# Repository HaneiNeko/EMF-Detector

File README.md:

# EMF Detector

Original project : https://www.instructables.com/Attiny85-EMF-detector/

## What is an EMF detector ?
An EMF detector is a device used to measure the presence and intensity of electromagnetic fields in a particular area.

Using in the ghosts detection 👻, this device is very famous.

## How does it work ?
An antena detect a electromagnetic fields, and depending on the electromagnetic field's force, a led will be turn on, and make a noise.

## This project
This project is an EMF detector using the Arduino framework.

## Schematics

## Usage
1. Use the schematic for create the PCB
2. Push the code into the microcontroller
3. Print the case (optional)
4. Enjoy ! 👻😉

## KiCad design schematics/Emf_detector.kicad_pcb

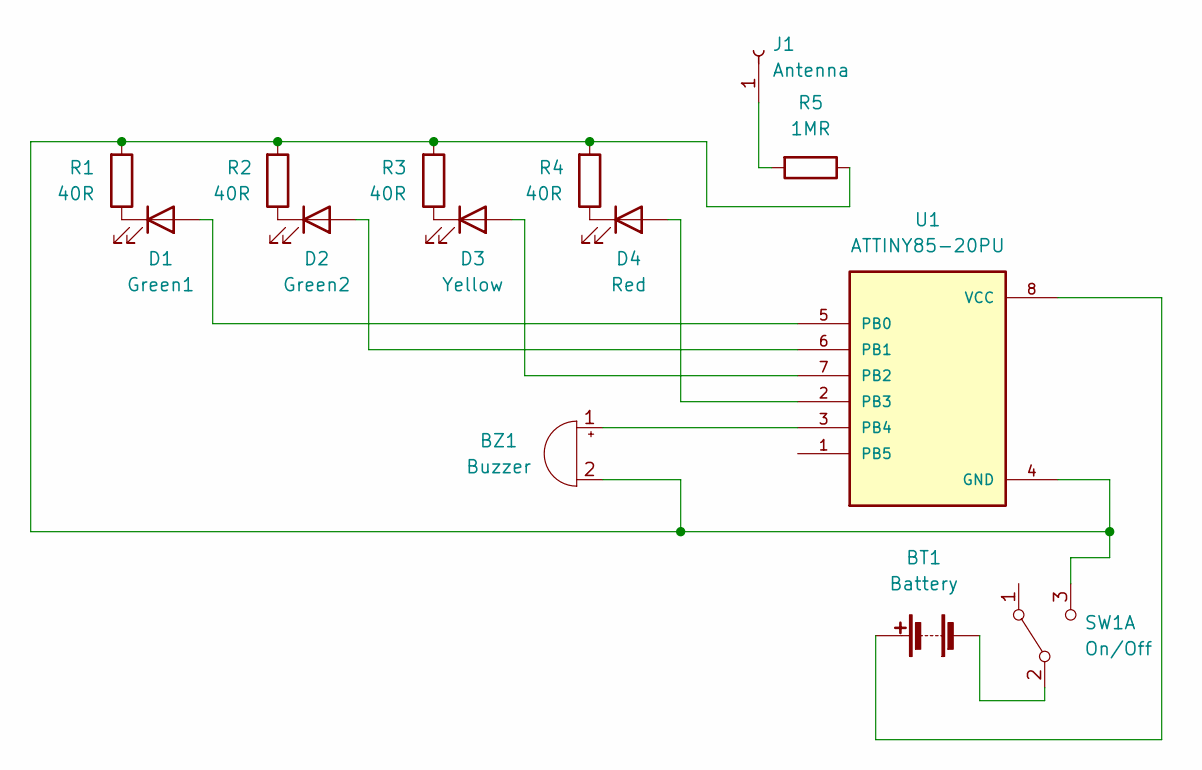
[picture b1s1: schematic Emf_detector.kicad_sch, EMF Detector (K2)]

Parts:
BT1: Battery; BatteryHolder_MPD_BC2003_1x2032
BZ1: Buzzer; Buzzer_12x9.5RM7.6
D1: Green1; LED_D3.0mm
D2: Green2; LED_D3.0mm
D3: Yellow; LED_D3.0mm
D4: Red; LED_D3.0mm
J1: Antenna; PinHeader_1x01_P1.00mm_Vertical
R1, R2, R3, R4: 40R; R_Axial_DIN0309_L9.0mm_D3.2mm_P12.70mm_Horizontal
R5: 1MR; R_Axial_DIN0309_L9.0mm_D3.2mm_P12.70mm_Horizontal
SW1: On/Off; SW_CuK_OS102011MA1QN1_SPDT_Angled
U1: ATTINY85-20PU; DIP762W46P254L927H533Q8B

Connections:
unnamed: BT1.1 (+), U1.8 (VCC)
unnamed: BT1.2 (-), SW1.2 (B)
unnamed: BZ1.1 (-), U1.3 (PB4)
unnamed: BZ1.2 (+), R1.2, R2.2, R3.2, R4.2, R5.1, SW1.3 (C), U1.4 (GND)
unnamed: D1.1 (K), R1.1
unnamed: D1.2 (A), U1.5 (PB0)
unnamed: D2.1 (K), R2.1
unnamed: D2.2 (A), U1.6 (PB1)
unnamed: D3.1 (K), R3.1
unnamed: D3.2 (A), U1.7 (PB2)
unnamed: D4.1 (K), R4.1
unnamed: D4.2 (A), U1.2 (PB3)
unnamed: J1.1, R5.2

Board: 2 copper layers, 14 parts (1 on the bottom side), 13 nets, no tracks yet.

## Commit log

2025-06-16 Create a readme file
2025-06-16 Add badges
2025-06-16 Add schematics
2025-06-16 Upgrade the file tree
2025-06-17 Upgrade schematics
2025-06-17 Remove Content part
2025-06-17 Add schematics image
2025-06-17 Add images file
